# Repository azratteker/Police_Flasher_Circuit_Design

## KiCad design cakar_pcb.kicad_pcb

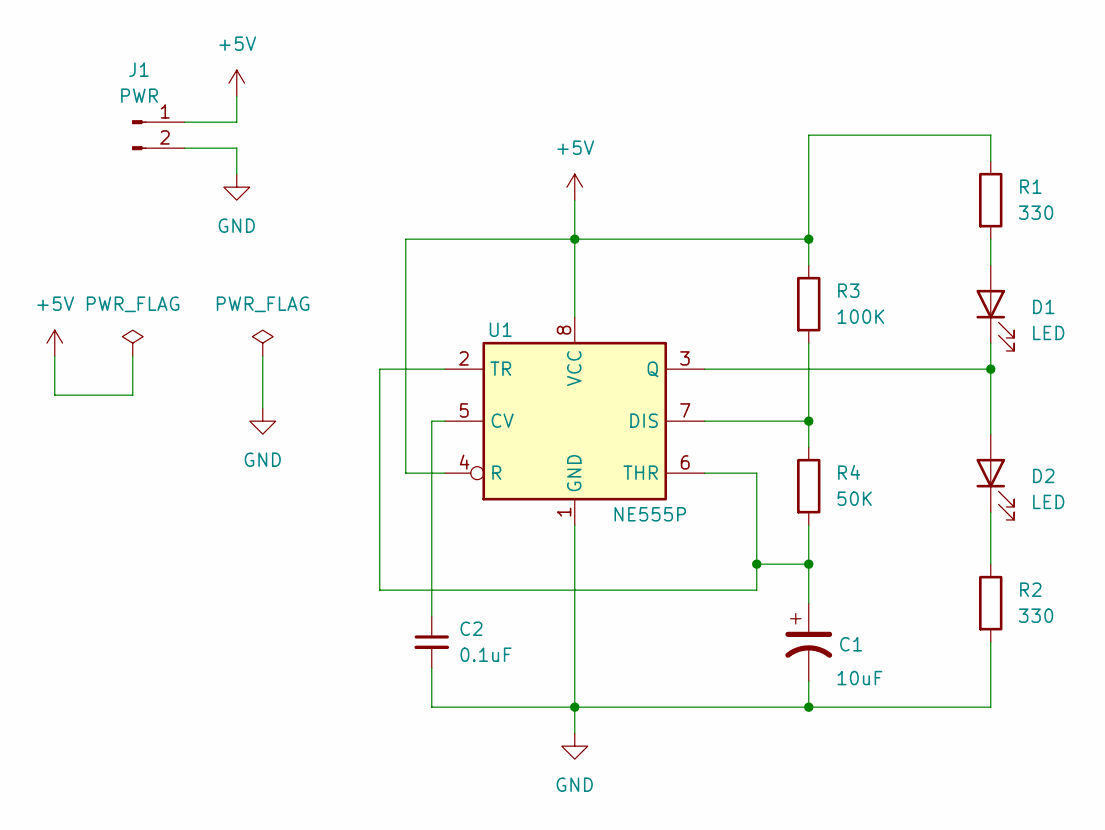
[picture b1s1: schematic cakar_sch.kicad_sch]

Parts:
C1: 10uF; CP_Radial_D6.3mm_P2.50mm
C2: 0.1uF; C_Disc_D3.0mm_W2.0mm_P2.50mm
D1, D2: LED; LED_D3.0mm
J1: PWR; Molex_KK-254_AE-6410-02A_1x02_P2.54mm_Vertical
R1, R2: 330; R_Axial_DIN0204_L3.6mm_D1.6mm_P5.08mm_Horizontal
R3: 100K; R_Axial_DIN0204_L3.6mm_D1.6mm_P5.08mm_Horizontal
R4: 50K; R_Axial_DIN0204_L3.6mm_D1.6mm_P5.08mm_Horizontal
U1: NE555P; DIP-8_W7.62mm

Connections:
+5V: J1.1, R1.1, R3.1, U1.4 (R), U1.8 (VCC)
GND: C1.2, C2.2, J1.2, R2.2, U1.1 (GND)
unnamed: D1.2 (A), R1.2
unnamed: D1.1 (K), D2.2 (A), U1.3 (Q)
unnamed: D2.1 (K), R2.1
unnamed: C2.1, U1.5 (CV)
unnamed: R3.2, R4.1, U1.7 (DIS)
unnamed: C1.1, R4.2, U1.2 (TR), U1.6 (THR)

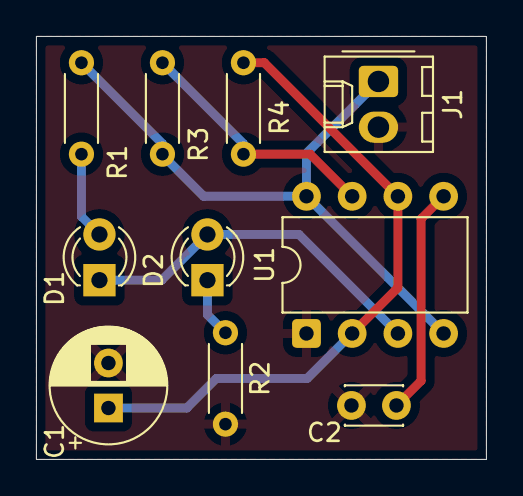
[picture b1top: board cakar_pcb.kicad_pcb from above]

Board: 2 copper layers, 25.0 x 23.5 mm, 10 parts (0 on the bottom side), 8 nets.

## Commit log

2025-09-29 Initial commit.
